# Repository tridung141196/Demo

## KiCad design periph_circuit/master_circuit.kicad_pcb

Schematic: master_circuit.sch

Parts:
C1, C2, C4, C5, C6, C7: 10uF; C_0805_2012Metric
C3: C_Small; C_0603_1608Metric
D1: LED; LED_0603_1608Metric
J1: Conn_01x06; PinHeader_1x06_P2.54mm_Vertical
J2: Conn_01x03; PinHeader_1x03_P2.54mm_Vertical
J3, J4: Conn_01x02; PinHeader_1x02_P2.54mm_Vertical
R1: 1k; R_0603_1608Metric
R2, R3, R4, R5, R6, R7: 10k; R_0603_1608Metric
U1: ESP-12E; ESP-12E_SMD
U2: AMS1117-5V; SOT-223
U3: AMS1117-3V3; SOT-223

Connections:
+3V3: C1.1, C2.1, C7.1, J1.1, J3.1, R2.2, R3.2, R4.2, R5.2, U1.8, U3.2 (VO)
+5V: C6.1, D1.2, J2.1, U2.2 (VO), U3.3 (VI)
ADC: J3.2, R7.1, U1.2
BAT: C4.1, J4.1, U2.3 (VI)
EN: J1.6, R5.1, U1.3
GND: C1.2, C2.2, C3.2, C4.2, C6.2, C7.2, J1.2, J2.3, J4.2, R1.1, R6.2, R7.2, U1.9, U2.1 (ADJ), U3.1 (ADJ)
IO0: J1.5, R2.1, U1.11
IO2: R3.1, U1.12
IO15: R6.1, U1.10
IO16: J2.2, U1.4
unnamed: D1.1, R1.2
RST: C3.1, R4.1, U1.1
RXD: J1.4, U1.15
TXD: J1.3, U1.16

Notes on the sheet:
KHÓA LUẬN TỐT NGHIỆP VÕ TRÍ DŨNG 3114490015
SOURCE BLOCK
MCU BLOCK
CONTROL RELAY BLOCK
MOISTURE SENSOR
DHT SENSOR
POWER LED
FLASH HEADER

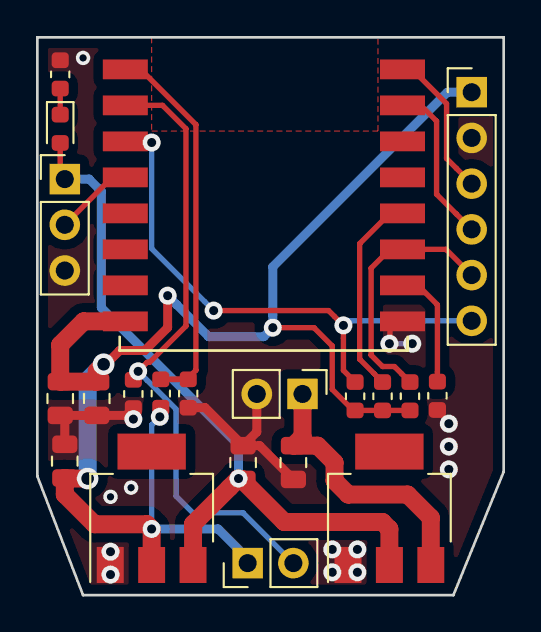
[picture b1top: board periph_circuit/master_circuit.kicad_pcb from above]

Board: 2 copper layers, 25.9 x 31.0 mm, 21 parts (0 on the bottom side), 14 nets.

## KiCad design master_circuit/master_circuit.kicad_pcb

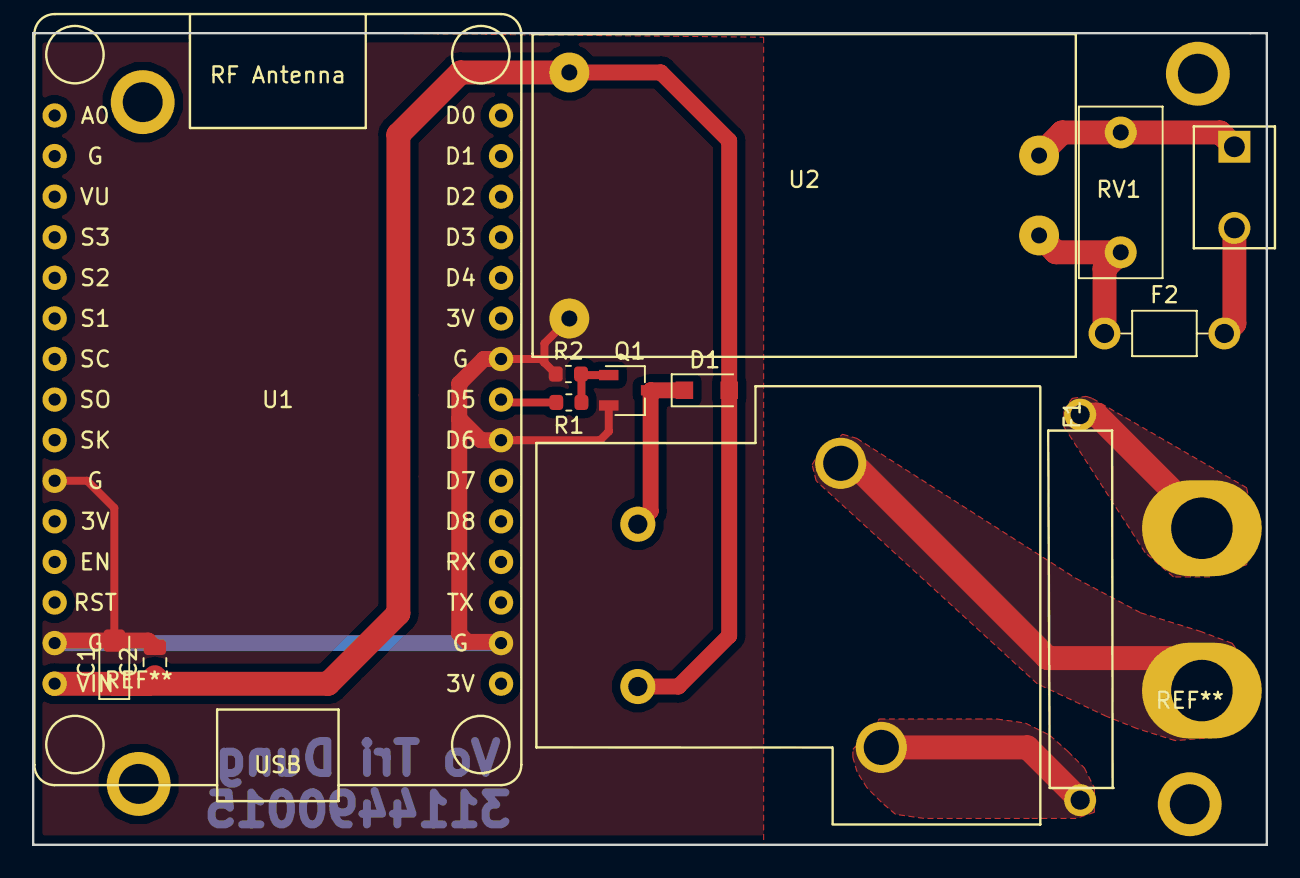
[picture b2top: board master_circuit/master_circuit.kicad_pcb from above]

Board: 2 copper layers, 77.2 x 50.8 mm, 15 parts (0 on the bottom side), 11 nets.

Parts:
C1: 10uF; CP_EIA-3216-12_Kemet-S
C2: 10uF; C_0805_2012Metric
D1: DIODE; D_SOD-123F
F1: Fuse; B78108E
F2: Fuse; C_Axial_L3.8mm_D2.6mm_P7.50mm_Horizontal
J1, J2: Conn_01x01; Hold_Pin_AC_SS
J3: Motor; PinSocket_1x02_P2.54mm_Vertical
K1: FINDER-32.21-x300; YX209E
Q1: 2N7002; TSOT-23
R1: 1k; R_0603_1608Metric
R2: 10k; R_0603_1608Metric
RV1: Varistor; C_Disc_D10.5mm_W5.0mm_P7.50mm
U1: NodeMCU1.0(ESP-12E); NodeMCU1.0(12-E)
U2: Hi-Link; HLK-PM

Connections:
GND: C1.2, C2.2, Q1.2, R2.1, U1.10, U1.14, U1.17, U1.22, U1.24, U2.3
IO14: R1.2, U1.23
unnamed: D1.1, K1.5, Q1.3
unnamed: F1.1, J1.1
unnamed: F1.2, K1.2
unnamed: F2.1, RV1.1, U2.1
unnamed: F2.2, J3.2
unnamed: J2.1, K1.3
unnamed: J3.1, RV1.2, U2.2
unnamed: Q1.1, R1.1, R2.2
Vin: C1.1, C2.1, D1.2, K1.1, U1.15, U2.4

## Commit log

2018-12-08 setup repo
2018-12-09 add design 2 pcb
